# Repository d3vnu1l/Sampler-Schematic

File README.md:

Sampler-Schematic made with eagle 8.4.1-1

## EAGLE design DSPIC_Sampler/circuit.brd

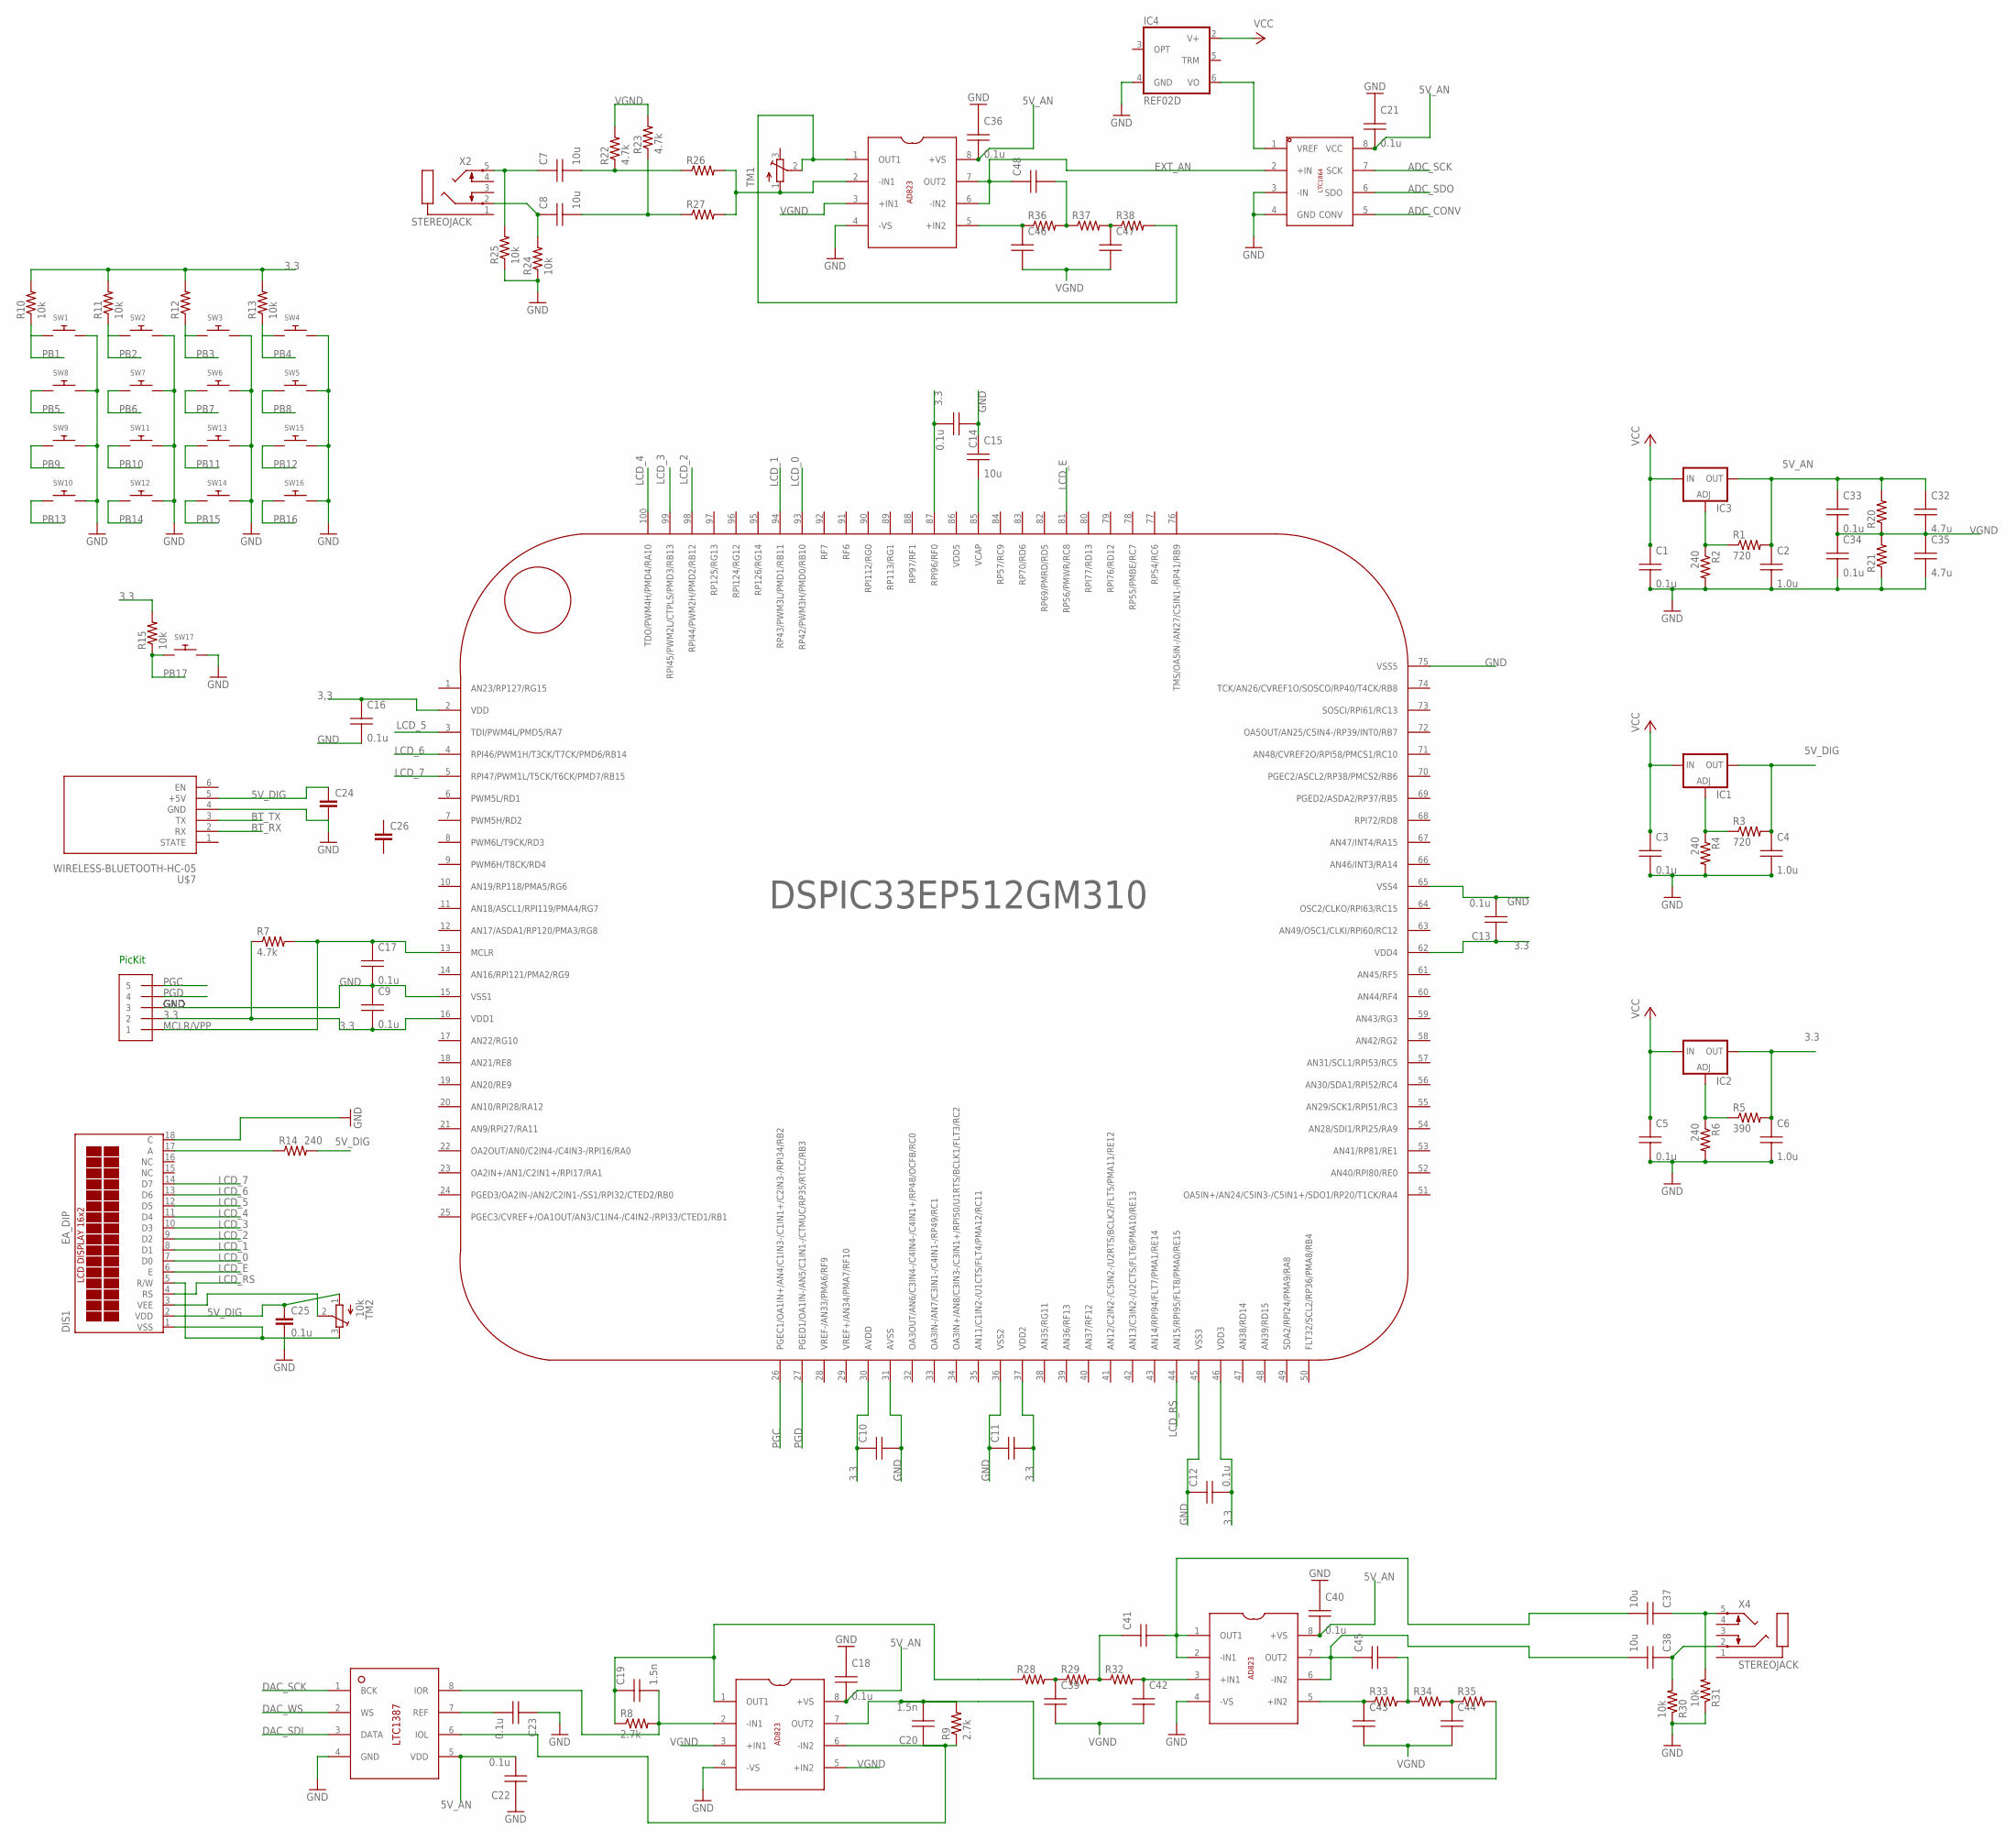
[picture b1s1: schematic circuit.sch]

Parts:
C1, C3, C5, C9, C12, C13, C14, C16, C17, C18, C21, C22, C23, C33, C34, C36, C40: 0.1u; C0805
C2, C4, C6: 1.0u; C0805
C7, C8, C15, C37, C38: 10u; C0805
C10, C11, C39, C41, C42, C43, C44, C45, C46, C47, C48: CAP; C0805
C19, C20: 1.5n; C0805
C24, C26: C5/5.5; C5B5.5
C25: 0.1u; C5B5.5
C32, C35: 4.7u; C0805
DIS1: EA_DIP
IC1, IC2, IC3: LM317TL; 317TL
IC4: REF02D; SO08
J1: 1X5; 1X05-3.5MM
R1, R3: 720; R0603
R2, R4, R6: 240; R0603
R5: 390; R0603
R7, R22, R23: 4.7k; R0603
R8, R9: 2.7k; R0603
R10, R11, R13, R15, R24, R25, R30, R31: 10k; R0603
R12, R14, R20, R21, R26, R27, R28, R29, R32, R33, R34, R35, R36, R37, R38: R-US_R0603; R0603
SW1, SW2, SW3, SW4, SW5, SW6, SW7, SW8, SW9, SW10, SW11, SW12, SW13, SW14, SW15, SW16, SW17: SWITCH_PUSHBUTTONC&K_KSS; BTN_CK_KSS
TM1: TRIMPOTTC33X; TC33X
TM2: 10k; TC33X
U$1: DSPIC33EP512GM310; TQFP-100
U$2, U$4, U$5: AD823; SOIC-8-AD
U$3: LTC1864; MSOP-8
U$6: TDA1387; SO-8
U$7: WIRELESS-BLUETOOTH-HC-05
X2, X4: STEREOJACK; STX3100

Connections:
3,3: C16.1 (A)
3.3: C6.1 (A), C9.2 (B), C10.1 (A), C11.2 (B), C12.2 (B), C13.1 (A), C14.2 (B), IC2.2 (OUT), J1.2, R5.2, R7.1, R10.2, R11.2, R12.2, R13.2, R15.2, U$1.16 (VDD1), U$1.62 (VDD4); also elsewhere on the board
5V_AN: C2.1 (A), C18.2 (B), C21.2 (B), C22.2 (B), C32.1 (A), C33.1 (A), C36.2 (B), C40.2 (B), IC3.2 (OUT), R1.2, R20.2, U$2.8 (+VS), U$3.8 (VCC), U$4.8 (+VS), U$5.8 (+VS), U$6.5 (VDD)
5V_DIG: C4.1 (A), C24.1, C25.1, DIS1.2 (VDD), IC1.2 (OUT), R3.2, R14.2, TM2.1 (A), U$7.5 (+5V)
ADC_CONV: U$3.5 (CONV)
ADC_SCK: U$3.7 (SCK)
ADC_SDO: U$3.6 (SDO)
BT_RX: U$7.2 (RX)
BT_TX: U$7.3 (TX)
DAC_SCK: U$6.1 (BCK)
DAC_SDI: U$6.3 (DATA)
DAC_WS: U$6.2 (WS)
EXT_AN: C48.1 (A), U$3.2 (+IN), U$4.6 (-IN2), U$4.7 (OUT2)
GND: C1.2 (B), C2.2 (B), C3.2 (B), C4.2 (B), C5.2 (B), C6.2 (B), C9.1 (A), C10.2 (B), C11.1 (A), C12.1 (A), C13.2 (B), C14.1 (A), C15.1 (A), C16.2 (B), C17.2 (B), C18.1 (A), C21.1 (A), C22.1 (A), C23.1 (A), C25.2, C34.2 (B), C35.2 (B), C36.1 (A), C40.1 (A), DIS1.18 (C), IC4.4 (GND), J1.3, R2.2, R4.2, R6.2, R21.1, R24.1, R25.1, R30.1, R31.1, SW1.P$2, SW2.P$2, SW3.P$2, SW4.P$2, SW5.P$2, SW6.P$2, SW7.P$2, SW8.P$2, SW9.P$2, SW10.P$2, SW11.P$2, SW12.P$2, SW13.P$2, SW14.P$2, SW15.P$2, SW16.P$2, SW17.P$2, TM2.3 (E), U$1.15 (VSS1), U$1.65 (VSS4), U$1.75 (VSS5), U$2.4 (-VS), U$3.3 (-IN), U$3.4 (GND), U$4.4 (-VS), U$5.4 (-VS), U$6.4 (GND); also elsewhere on the board
GND1: R10.1, R11.1, R12.1, R13.1
LCD_0: DIS1.7 (D0), U$1.93 (RP42/PWM3H/PMD0/RB10)
LCD_1: DIS1.8 (D1)
LCD_2: DIS1.9 (D2)
LCD_3: DIS1.10 (D3)
LCD_4: DIS1.11 (D4)
LCD_5: DIS1.12 (D5)
LCD_6: DIS1.13 (D6)
LCD_7: DIS1.14 (D7)
LCD_E: DIS1.6 (E)
LCD_RS: DIS1.4 (RS)
MCLR/VPP: C17.1 (A), J1.1, R7.2, U$1.13 (MCLR)
unnamed: IC3.1 (ADJ), R1.1, R2.1
unnamed: C15.2 (B), U$1.85 (VCAP)
unnamed: IC1.1 (ADJ), R3.1, R4.1
unnamed: IC2.1 (ADJ), R5.1, R6.1
unnamed: C7.1 (A), R25.2, X2.5
unnamed: C8.1 (A), R24.2, X2.2
unnamed: C19.2 (B), R8.2, U$2.2 (-IN1), U$6.8 (IOR)
unnamed: C19.1 (A), R8.1, U$2.1 (OUT1)
unnamed: C20.1 (A), R9.1, U$2.6 (-IN2), U$6.6 (IOL)
unnamed: C20.2 (B), R9.2, U$2.7 (OUT2)
unnamed: C37.1 (A), R31.2, X4.5
unnamed: R38.2, TM1.2 (S), U$4.1 (OUT1)
unnamed: C7.2 (B), R22.1, R26.1
unnamed: C8.2 (B), R23.1, R27.1
unnamed: R26.2, R27.2, TM1.1 (A), U$4.2 (-IN1)
unnamed: C38.1 (A), R30.2, X4.2
unnamed: C39.1 (A), R28.2, R29.1
unnamed: C41.1 (A), R29.2, R32.1
unnamed: C37.2 (B), C41.2 (B), U$5.1 (OUT1), U$5.2 (-IN1)
unnamed: C38.2 (B), C45.1 (A), U$5.6 (-IN2), U$5.7 (OUT2)
unnamed: C45.2 (B), R33.2, R34.1
unnamed: C44.1 (A), R34.2, R35.1
unnamed: C42.1 (A), R32.2, U$5.3 (+IN1)
unnamed: C43.1 (A), R33.1, U$5.5 (+IN2)
unnamed: C23.2 (B), U$6.7 (REF)
unnamed: IC4.6 (VO), U$3.1 (VREF)
unnamed: C48.2 (B), R36.2, R37.1
unnamed: C47.1 (A), R37.2, R38.1
unnamed: C46.1 (A), R36.1, U$4.5 (+IN2)
unnamed: DIS1.1 (VSS), DIS1.5 (R/W)
unnamed: DIS1.3 (VEE), TM2.2 (S)
unnamed: DIS1.17 (A), R14.1
PB_1: SW1.P$1, U$1.90 (RPI112/RG0)
PB_2: SW2.P$1
PB_3: SW3.P$1
PB_4: SW4.P$1
PB_5: SW8.P$1
PB_6: SW7.P$1
PB_7: SW6.P$1
PB_8: SW5.P$1
PB_9: SW9.P$1
PB_10: SW11.P$1
PB_11: SW13.P$1
PB_12: SW15.P$1
PB_13: SW10.P$1
PB_14: SW12.P$1
PB_15: SW14.P$1
PB_16: SW16.P$1
PB_17: R15.1, SW17.P$1
PGC: J1.5, U$1.26 (PGEC1/OA1IN+/AN4/C1IN3-/C1IN1+/C2IN3-/R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)
PGD: J1.4, U$1.27 (PGED1/OA1IN-/AN5/C1IN1-/CTMUC/RP35/RTCC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)
POT_1: U$1.22 (OA2OUT/AN0/C2IN4-/C4IN3-/RPI16/RA0); also elsewhere on the board
POT_2: U$1.23 (OA2IN+/AN1/C2IN1+/RPI17/RA1); also elsewhere on the board
POT_3: U$1.25 (PGEC3/CVREF+/OA1OUT/AN3/C1IN4-/C4IN2-/R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); also elsewhere on the board
VCC: C1.1 (A), C3.1 (A), C5.1 (A), IC1.3 (IN), IC2.3 (IN), IC3.3 (IN), IC4.2 (V+)
VGND: C32.2 (B), C33.2 (B), C34.1 (A), C35.1 (A), C39.2 (B), C42.2 (B), C43.2 (B), C44.2 (B), C46.2 (B), C47.2 (B), R20.1, R21.2, R22.2, R23.2, U$2.3 (+IN1), U$2.5 (+IN2), U$4.3 (+IN1)

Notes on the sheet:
PicKit

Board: 2 copper layers, 116 parts (0 on the bottom side), 49 nets, no tracks yet.

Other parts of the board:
TM3, TM4, TM5, TM6, TM7, TM8: 10k; TC33X

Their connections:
3.3: TM3.1, TM4.1, TM5.1, TM6.1, TM7.1, TM8.1; also elsewhere on the board
GND: TM3.3, TM4.3, TM5.3, TM6.3, TM7.3, TM8.3; also elsewhere on the board
POT_1: TM6.2; also elsewhere on the board
POT_2: TM3.2; also elsewhere on the board
POT_3: TM7.2; also elsewhere on the board

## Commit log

2017-11-12 Pushed initial circuit files
2017-11-12 Add ADC and I/V stage
2017-11-13 Added DAC and finished ADC/DAC
2017-11-15 Resized, added label for rafi
2017-11-21 Added HC-05 bt
2017-11-22 Swap lcd and fixed potentiometer wiring
2017-11-22 More cap/resistor values
2017-11-22 LCD is connected
2017-11-22 Added pots
    not all connected yet
2017-11-22 Created and added serial memory device
2017-11-22 Connected adc/dac and memory to mcu
2017-11-22 Added text labels
2017-11-22 shrunk schematic
2018-01-14 Pin changes
2018-01-14 Pushbutton pin changes
2018-01-19 Pad pin changes
2018-01-27 Pin changes for pots, SPI3_mem
2018-01-29 Added Encoder pinout
    Still needs encoder model
2018-02-06 Updated pinout for flash memory
2018-02-24 Added pins for RGB led
2018-03-06 printer friendly

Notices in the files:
parts and their libraries:
diy-modules: Released under the Creative Commons Attribution 4.0 International License: http://creativecommons.org/licenses/by/4.0
